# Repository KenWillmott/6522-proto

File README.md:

# 6522-proto
This M8 bus compatible card combines a 6522 VIA multi-IO chip with a prototyping area and some I/O connector footprints.
[https://github.com/KenWillmott/6522-proto/blob/main/cpu-6502-production-2023-12-04.png](https://github.com/KenWillmott/6522-proto/blob/main/cpu-6502-production-2023-12-04.png?raw=true)

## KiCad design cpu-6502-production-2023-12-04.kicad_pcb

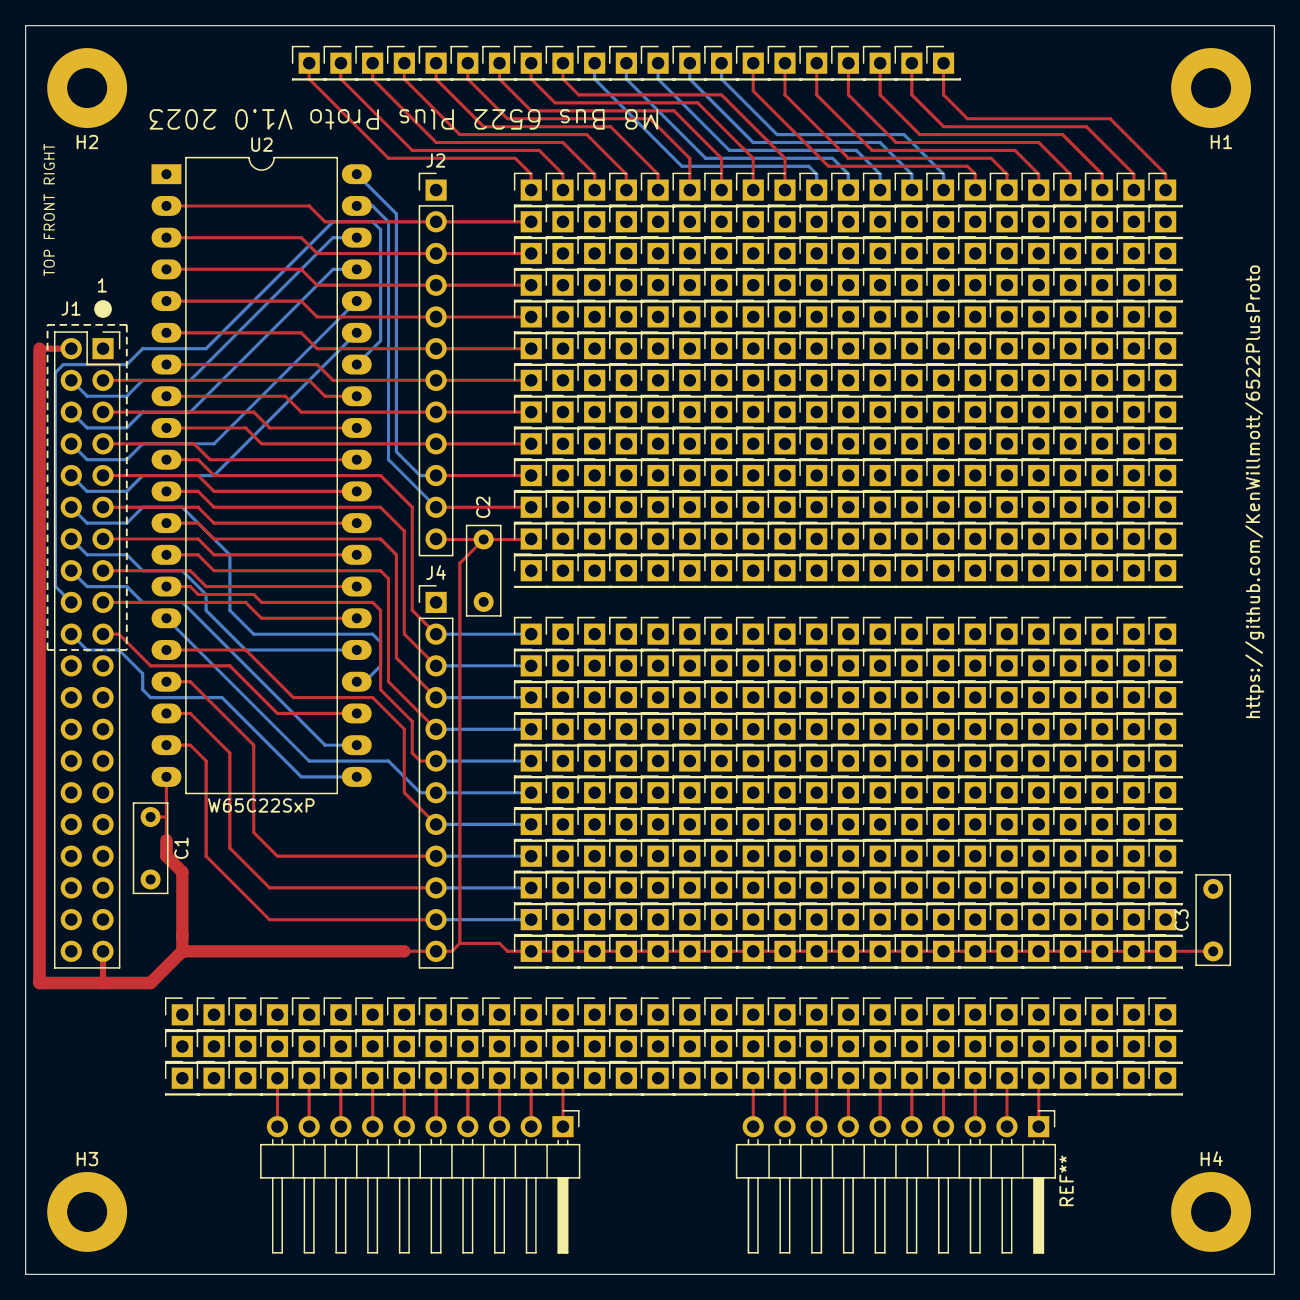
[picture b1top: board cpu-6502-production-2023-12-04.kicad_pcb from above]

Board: 2 copper layers, 100.0 x 100.0 mm, 11 parts (0 on the bottom side), 40 nets.

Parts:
C1, C2, C3: 100n; C_Disc_D7.0mm_W2.5mm_P5.00mm
H1, H2, H3, H4: MountingHole_Pad; MountingHole_3.2mm_M3_Pad
J1: Conn_02x20_Odd_Even; PinSocket_2x20_P2.54mm_Vertical
J2, J4: Conn_01x12_Pin; PinHeader_1x12_P2.54mm_Vertical
U2: W65C22SxP; DIP-40_W15.24mm_LongPads

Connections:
/A0: J1.4, U2.38 (RS0)
/A1: J1.6, U2.37 (RS1)
/A2: J1.8, U2.36 (RS2)
/A3: J1.10, U2.35 (RS3)
/A4: J1.12, U2.24 (CS1)
/D0: J1.3, U2.33 (D0)
/D1: J1.5, U2.32 (D1)
/D2: J1.7, U2.31 (D2)
/D3: J1.9, U2.30 (D3)
/D4: J1.11, U2.29 (D4)
/D5: J1.13, U2.28 (D5)
/D6: J1.15, U2.27 (D6)
/D7: J1.17, U2.26 (D7)
/bus/BSEL0*: J1.19, U2.23 (~CS2)
/bus/E: J1.14, U2.25 (ϕ2)
/bus/IRQ: J1.20, U2.21 (~IRQ)
/bus/RES: J1.18, U2.34 (~RES)
/bus/RW: J1.16, U2.22 (R/~W)
GND: C1.2, C2.2, C3.2, H1.1, H2.1, H3.1, H4.1, J1.1, J1.40, J2.1, J4.1, U2.1 (VSS)
unnamed: J2.2, U2.2 (PA0)
unnamed: J2.3, U2.3 (PA1)
unnamed: J2.4, U2.4 (PA2)
unnamed: J2.5, U2.5 (PA3)
unnamed: J2.6, U2.6 (PA4)
unnamed: J2.7, U2.7 (PA5)
unnamed: J2.8, U2.8 (PA6)
unnamed: J2.9, U2.9 (PA7)
unnamed: J2.10, U2.40 (CA1)
unnamed: J2.11, U2.39 (CA2)
unnamed: J4.2, U2.10 (PB0)
unnamed: J4.3, U2.11 (PB1)
unnamed: J4.4, U2.12 (PB2)
unnamed: J4.5, U2.13 (PB3)
unnamed: J4.6, U2.14 (PB4)
unnamed: J4.7, U2.15 (PB5)
unnamed: J4.8, U2.16 (PB6)
unnamed: J4.9, U2.17 (PB7)
unnamed: J4.10, U2.18 (CB1)
unnamed: J4.11, U2.19 (CB2)
VCC: C1.1, C2.1, C3.1, J1.2, J1.39, J2.12, J4.12, U2.20 (VCC)
